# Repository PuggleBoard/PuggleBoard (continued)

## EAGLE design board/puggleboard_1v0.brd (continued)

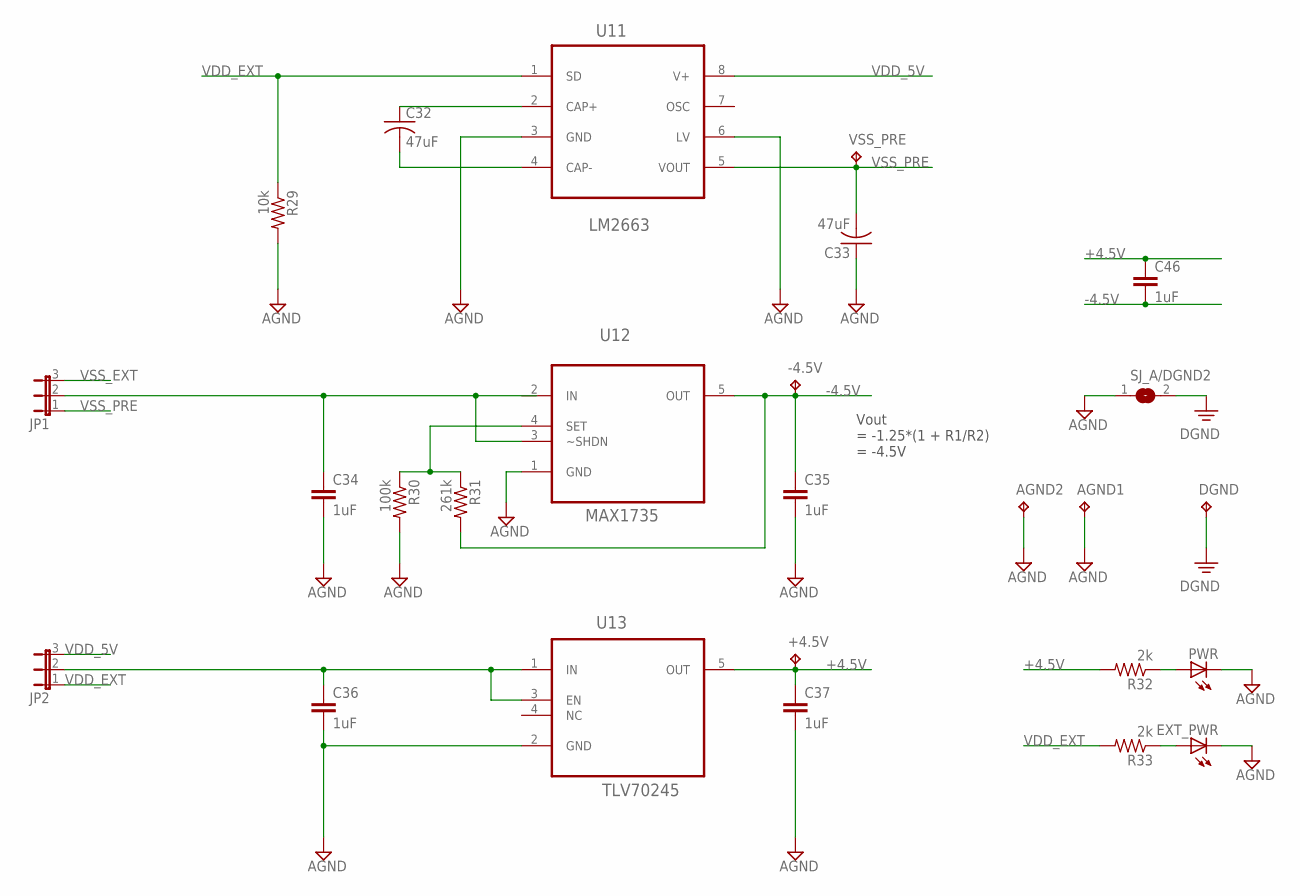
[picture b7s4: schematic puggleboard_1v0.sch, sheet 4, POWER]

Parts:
+4.5V: TPPAD1-17; P1-17
-4.5V: TPB1,27; B1,27
AGND1, AGND2: TPPAD1-17; P1-17
C32, C33: 47uF; C1206
C34, C35, C36, C37, C46: 1uF; C0603
DGND: TPPAD1-17; P1-17
EXT_PWR: LEDCHIPLED_0805; CHIPLED_0805
JP1, JP2: JP2E; JP2
PWR: LEDCHIPLED_0805; CHIPLED_0805
R29: 10k; R0603
R30: 100k; R0603
R31: 261k; R0603
R32, R33: 2k; R0603
SJ_A/DGND2: SJ
U11: LM2663; SOIC127P600X175-8N
U12: MAX1735; SOT95P280X145-5N
U13: TLV70245; SOT95P280X110-5N
VSS_PRE: TPB1,27; B1,27

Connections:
+4.5V: +4.5V.TP, C37.1, C46.1, R32.2, U13.5 (OUT); also elsewhere on the board
-4.5V: -4.5V.TP, C35.1, C46.2, R31.2, U12.5 (OUT); also elsewhere on the board
AGND: AGND1.TP, AGND2.TP, C33.1, C34.2, C35.2, C36.2, C37.2, EXT_PWR.C, PWR.C, R29.2, R30.2, SJ_A/DGND2.1, U11.3 (GND), U11.6 (LV), U12.1 (GND), U13.2 (GND); also elsewhere on the board
DGND: DGND.TP, SJ_A/DGND2.2; also elsewhere on the board
unnamed: R30.1, R31.1, U12.4 (SET)
unnamed: EXT_PWR.A, R33.1
unnamed: C36.1, JP2.2, U13.1 (IN), U13.3 (EN)
unnamed: PWR.A, R32.1
unnamed: C34.1, JP1.2, U12.3 (~SHDN)
unnamed: C32.1, U11.2 (CAP+)
unnamed: C32.2, U11.4 (CAP-)
VDD_5V: JP2.3, U11.8 (V+); also elsewhere on the board
VDD_EXT: JP2.1, R29.1, R33.2, U11.1 (SD); also elsewhere on the board
VSS_EXT: JP1.3; also elsewhere on the board
VSS_PRE: C33.2, JP1.1, U11.5 (VOUT), VSS_PRE.TP

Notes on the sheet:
Vout = -1.25*(1 + R1/R2) = -4.5V

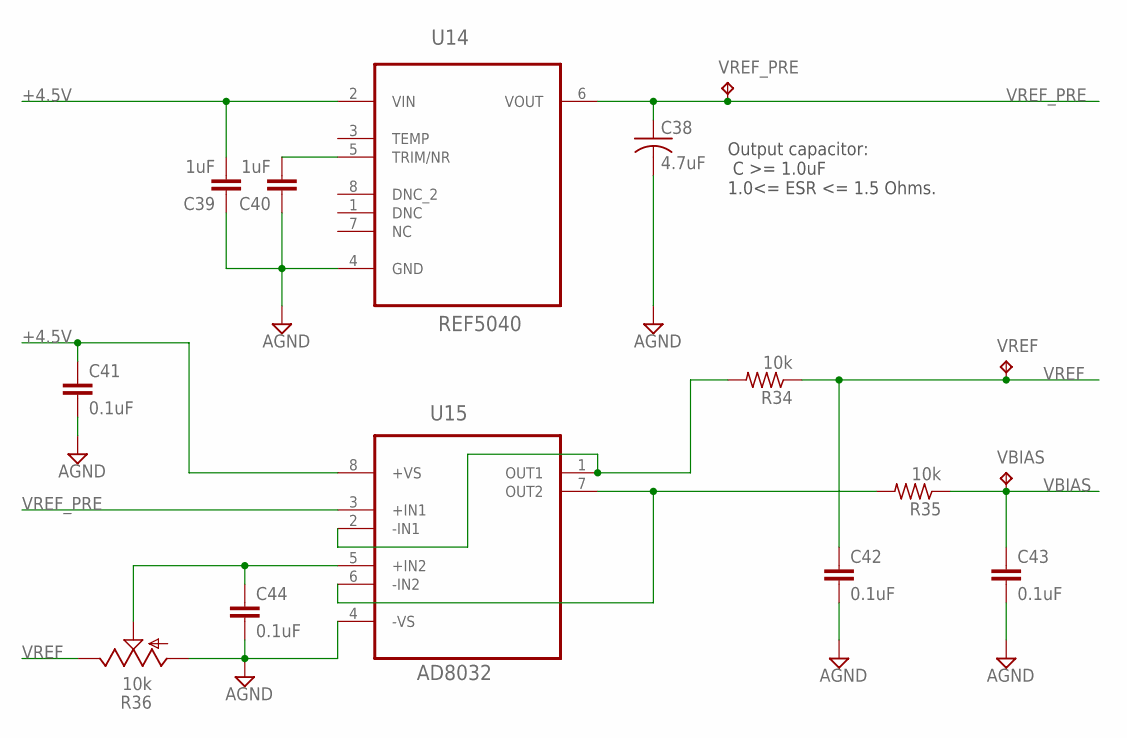
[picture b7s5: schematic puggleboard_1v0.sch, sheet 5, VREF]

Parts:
C38: 4.7uF; C1206
C39, C40: 1uF; C0603
C41, C42, C43, C44: 0.1uF; C0603
R34, R35: 10k; R0603
R36: 10k; M84W-TRIMMER
U14: REF5040; SOIC127P600X175-8N
U15: AD8032; SOIC127P600X175-8N
VBIAS: TPB1,27; B1,27
VREF: TPB1,27; B1,27
VREF_PRE: TPB1,27; B1,27

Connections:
+4.5V: C39.2, C41.1, U14.2 (VIN), U15.8 (+VS); also elsewhere on the board
AGND: C38.2, C39.1, C40.1, C41.2, C42.2, C43.2, C44.2, R36.3 (A), U14.4 (GND), U15.4 (-VS); also elsewhere on the board
unnamed: C44.1, R36.2 (S), U15.5 (+IN2)
unnamed: R35.2, U15.6 (-IN2), U15.7 (OUT2)
unnamed: R34.2, U15.1 (OUT1), U15.2 (-IN1)
unnamed: C40.2, U14.5 (TRIM/NR)
VBIAS: C43.1, R35.1, VBIAS.TP; also elsewhere on the board
VREF: C42.1, R34.1, R36.1 (E), VREF.TP; also elsewhere on the board
VREF_PRE: C38.1, U14.6 (VOUT), U15.3 (+IN1), VREF_PRE.TP

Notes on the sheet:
Output capacitor: C >= 1.0uF 1.0<= ESR <= 1.5 Ohms.

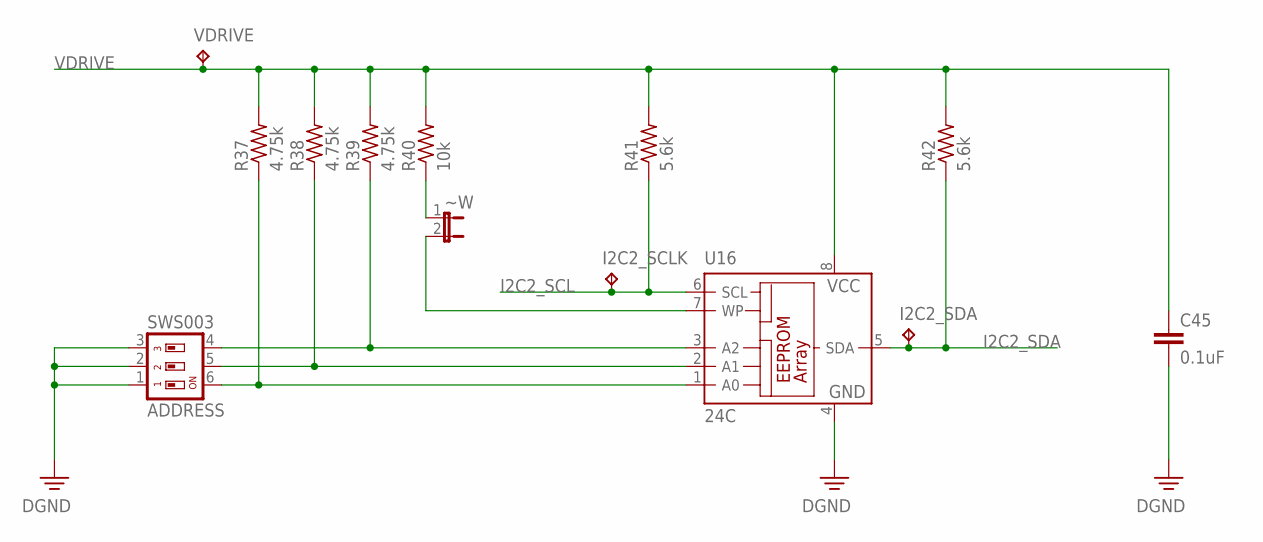
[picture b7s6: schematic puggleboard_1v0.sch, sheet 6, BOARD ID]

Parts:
ADDRESS: SWS003; SMS-003
C45: 0.1uF; C0603
I2C2_SCLK, I2C2_SDA: TPB1,27; B1,27
R37, R38, R39: 4.75k; R0603
R40: 10k; R0603
R41, R42: 5.6k; R0603
U16: 24C; SO-08
VDRIVE: TPPAD1-17; P1-17
~W: JP1E; JP1

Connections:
DGND: ADDRESS.1, ADDRESS.2, ADDRESS.3, C45.2, U16.4 (GND); also elsewhere on the board
I2C2_SCL: I2C2_SCLK.TP, R41.1, U16.6 (SCL); also elsewhere on the board
I2C2_SDA: I2C2_SDA.TP, R42.1, U16.5 (SDA); also elsewhere on the board
unnamed: ADDRESS.6, R37.1, U16.1 (A0)
unnamed: ADDRESS.5, R38.1, U16.2 (A1)
unnamed: ADDRESS.4, R39.1, U16.3 (A2)
unnamed: U16.7 (WP), ~W.2
unnamed: R40.1, ~W.1
VDRIVE: C45.1, R37.2, R38.2, R39.2, R40.2, R41.2, R42.2, U16.8 (VCC), VDRIVE.TP; also elsewhere on the board

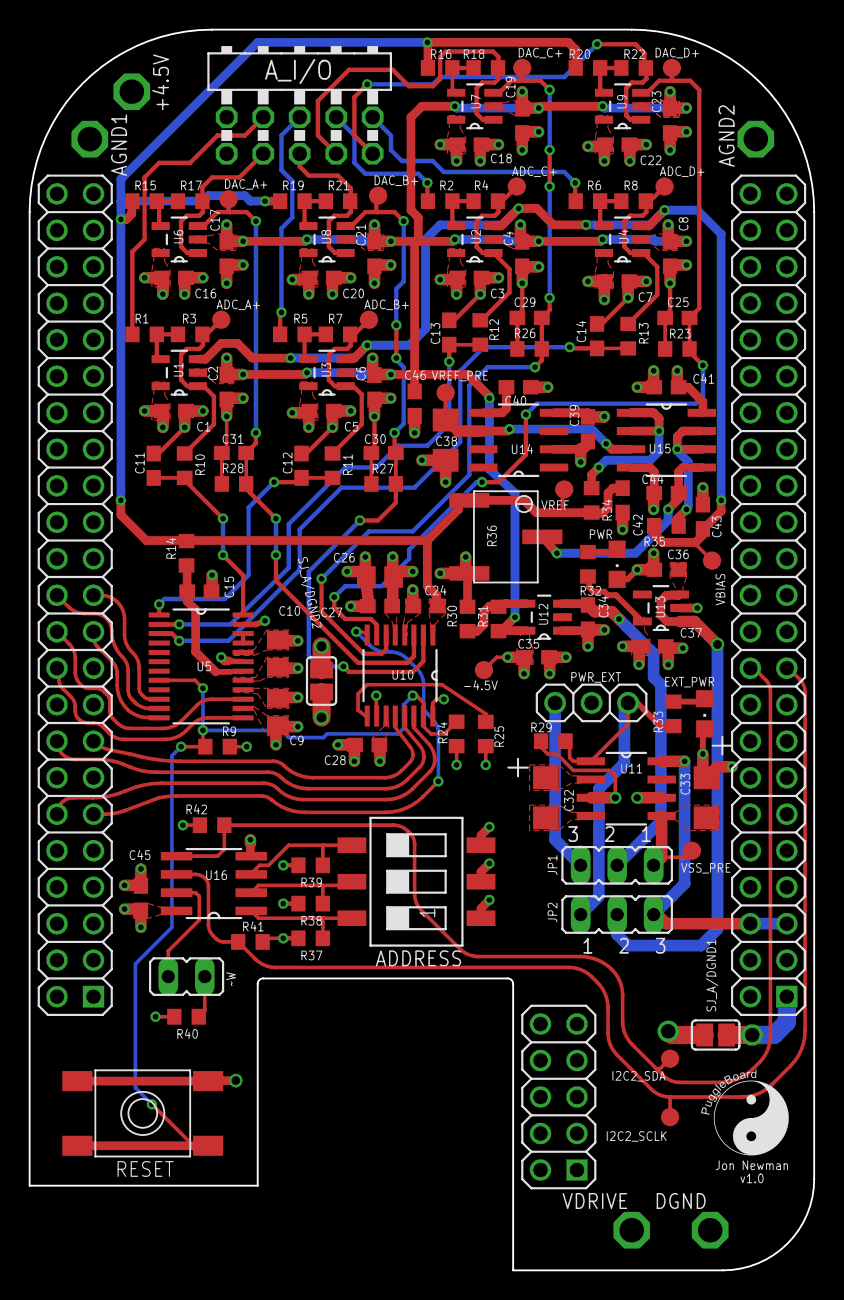
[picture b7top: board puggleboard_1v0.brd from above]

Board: 4 copper layers, 54.6 x 86.4 mm, 136 parts (0 on the bottom side), 73 nets.

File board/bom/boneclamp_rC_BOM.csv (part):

Part,Value,Device,Package,Description,MPN,DKN,,,Manu
ADDRESS,SWS003,SWS003,SMS-003,SMD Dip Switch 3 pol.,219-3LPST,CT2193LPST-ND,,,
A_I/O,PINHD-2X5/90,PINHD-2X5/90,2X05/90,2X5 0.1 inch male header,68021-210HLF,609-3410-ND,,,
C1,0.1uF,C-EUC0603,C0603,"CAPACITOR, European symbol",C1608X7R1E104K080AA,445-1316-1-ND,,,
C2,0.1uF,C-EUC0603,C0603,"CAPACITOR, European symbol",C1608X7R1E104K080AA,445-1316-1-ND,,,
C3,0.1uF,C-EUC0603,C0603,"CAPACITOR, European symbol",C1608X7R1E104K080AA,445-1316-1-ND,,,
C4,0.1uF,C-EUC0603,C0603,"CAPACITOR, European symbol",C1608X7R1E104K080AA,445-1316-1-ND,,,
C5,0.1uF,C-EUC0603,C0603,"CAPACITOR, European symbol",C1608X7R1E104K080AA,445-1316-1-ND,,,
C6,0.1uF,C-EUC0603,C0603,"CAPACITOR, European symbol",C1608X7R1E104K080AA,445-1316-1-ND,,,
C7,0.1uF,C-EUC0603,C0603,"CAPACITOR, European symbol",C1608X7R1E104K080AA,445-1316-1-ND,,,
C8,0.1uF,C-EUC0603,C0603,"CAPACITOR, European symbol",C1608X7R1E104K080AA,445-1316-1-ND,,,
C9,4.7uF,C-EUC0805,C0805,"CAPACITOR, European symbol",TMK212AB7475KG-T,587-2990-1-ND,,,
C10,4.7uF,C-EUC0805,C0805,"CAPACITOR, European symbol",TMK212AB7475KG-T,587-2990-1-ND,,,
C11,1nF,C-EUC0603,C0603,"CAPACITOR, European symbol",C0603C102K3RACTU,399-7834-1-ND,,,
C12,1nF,C-EUC0603,C0603,"CAPACITOR, European symbol",C0603C102K3RACTU,399-7834-1-ND,,,
C13,1nF,C-EUC0603,C0603,"CAPACITOR, European symbol",C0603C102K3RACTU,399-7834-1-ND,,,
C14,1nF,C-EUC0603,C0603,"CAPACITOR, European symbol",C0603C102K3RACTU,399-7834-1-ND,,,
C15,22uF,C-EUC0603,C0603,"CAPACITOR, European symbol",C2012X5R1A226M125AB,445-7665-1-ND,,,
C16,0.1uF,C-EUC0603,C0603,"CAPACITOR, European symbol",C1608X7R1E104K080AA,445-1316-1-ND,,,
C17,0.1uF,C-EUC0603,C0603,"CAPACITOR, European symbol",C1608X7R1E104K080AA,445-1316-1-ND,,,
C18,0.1uF,C-EUC0603,C0603,"CAPACITOR, European symbol",C1608X7R1E104K080AA,445-1316-1-ND,,,
C19,0.1uF,C-EUC0603,C0603,"CAPACITOR, European symbol",C1608X7R1E104K080AA,445-1316-1-ND,,,
C20,0.1uF,C-EUC0603,C0603,"CAPACITOR, European symbol",C1608X7R1E104K080AA,445-1316-1-ND,,,
C21,0.1uF,C-EUC0603,C0603,"CAPACITOR, European symbol",C1608X7R1E104K080AA,445-1316-1-ND,,,
C22,0.1uF,C-EUC0603,C0603,"CAPACITOR, European symbol",C1608X7R1E104K080AA,445-1316-1-ND,,,
C23,0.1uF,C-EUC0603,C0603,"CAPACITOR, European symbol",C1608X7R1E104K080AA,445-1316-1-ND,,,
C24,0.1uF,C-EUC0603,C0603,"CAPACITOR, European symbol",C1608X7R1E104K080AA,445-1316-1-ND,,,
C25,,C-EUC0603,C0603,"CAPACITOR, European symbol",,,,,
C26,10uF,C-USC0805,C0805,"CAPACITOR, American symbol",TAJP106M010RNJ,478-3281-1-ND,,,
C27,0.1uF,C-EUC0603,C0603,"CAPACITOR, European symbol",C1608X7R1E104K080AA,445-1316-1-ND,,,
C28,0.1uF,C-EUC0603,C0603,"CAPACITOR, European symbol",C1608X7R1E104K080AA,445-1316-1-ND,,,
C29,,C-EUC0603,C0603,"CAPACITOR, European symbol",,,,,
C30,,C-EUC0603,C0603,"CAPACITOR, European symbol",,,,,
C31,,C-EUC0603,C0603,"CAPACITOR, European symbol",,,,,
C32,47uF,C-USC1206,C1206,"CAPACITOR, American symbol",T520A476M004ATE070,399-4714-1-ND,,,
C33,47uF,C-USC1206,C1206,"CAPACITOR, American symbol",T520A476M004ATE070,399-4714-1-ND,,,
C34,1uF,C-EUC0603,C0603,"CAPACITOR, European symbol",C0805C105K4RACTU,399-1284-1-ND,,,
C35,1uF,C-EUC0603,C0603,"CAPACITOR, European symbol",C0805C105K4RACTU,399-1284-1-ND,,,
C36,1uF,C-EUC0603,C0603,"CAPACITOR, European symbol",C0805C105K4RACTU,399-1284-1-ND,,,
C37,1uF,C-EUC0603,C0603,"CAPACITOR, European symbol",C0805C105K4RACTU,399-1284-1-ND,,,
C38,4.7uF,C-EUC0603,C1206,"CAPACITOR, European symbol",TR3A475K010C1400,718-1757-1-ND,,,
C39,1uF,C-EUC0603,C0603,"CAPACITOR, European symbol",C0805C105K4RACTU,399-1284-1-ND,,,
C40,1uF,C-EUC0603,C0603,"CAPACITOR, European symbol",C0805C105K4RACTU,399-1284-1-ND,,,
C41,0.1uF,C-EUC0603,C0603,"CAPACITOR, European symbol",C1608X7R1E104K080AA,445-1316-1-ND,,,
C42,0.1uF,C-EUC0603,C0603,"CAPACITOR, European symbol",C1608X7R1E104K080AA,445-1316-1-ND,,,
C43,0.1uF,C-EUC0603,C0603,"CAPACITOR, European symbol",C1608X7R1E104K080AA,445-1316-1-ND,,,
C44,0.1uF,C-EUC0603,"C0,603","CAPACITOR, European symbol",C1608X7R1E104K080AA,445-1316-1-ND,,,
C45,0.1uF,C-EUC0603,C0603,"CAPACITOR, European symbol",C1608X7R1E104K080AA,445-1316-1-ND,,,
EXT_PWR,,LEDCHIPLED_0805,CHIPLED_0805,LED,598-8140-107F,350-2041-1-ND,,,
JP1,,JP2E,JP2,JUMPER,87224-3,A26545-ND,,,
JP2,,JP2E,JP2,JUMPER,87224-3,A26545-ND,,,
JP3,,JP1E,JP1,JUMPER,87224-3,A26545-ND,,,
PWR,,LEDCHIPLED_0805,CHIPLED_0805,LED,598-8170-107F,350-2044-1-ND,,,
PWR_EXT,,PINHD-1X3,1X03,PIN HEADER,3M9468-ND,961103-5604-AR,,,
R1,20k,R-US_R0603,R0603,"RESISTOR, American symbol",MCT06030C2002FP500,MCT0603-20.0K-CFCT-ND,,,
R2,20k,R-US_R0603,R0603,"RESISTOR, American symbol",MCT06030C2002FP500,MCT0603-20.0K-CFCT-ND,,,
R3,10k,R-US_R0603,R0603,"RESISTOR, American symbol",MCT06030C1002FP500,MCT0603-10.0K-CFCT-ND,,,
R4,10k,R-US_R0603,R0603,"RESISTOR, American symbol",MCT06030C1002FP500,MCT0603-10.0K-CFCT-ND,,,
R5,20k,R-US_R0603,R0603,"RESISTOR, American symbol",MCT06030C2002FP500,MCT0603-20.0K-CFCT-ND,,,
R6,20k,R-US_R0603,R0603,"RESISTOR, American symbol",MCT06030C2002FP500,MCT0603-20.0K-CFCT-ND,,,
R7,10k,R-US_R0603,R0603,"RESISTOR, American symbol",MCT06030C1002FP500,MCT0603-10.0K-CFCT-ND,,,
R8,10k,R-US_R0603,R0603,"RESISTOR, American symbol",MCT06030C1002FP500,MCT0603-10.0K-CFCT-ND,,,
R9,10k,R-US_R0603,R0603,"RESISTOR, American symbol",CRCW060310K0JNEA,541-10KGCT-ND,,,
R10,20,R-US_R0603,R0603,"RESISTOR, American symbol",RMCF0603FT20R0,RMCF0603FT20R0CT-ND,,,
R11,20,R-US_R0603,R0603,"RESISTOR, American symbol",RMCF0603FT20R0,RMCF0603FT20R0CT-ND,,,
R12,20,R-US_R0603,R0603,"RESISTOR, American symbol",RMCF0603FT20R0,RMCF0603FT20R0CT-ND,,,
R13,20,R-US_R0603,R0603,"RESISTOR, American symbol",RMCF0603JT20R0,RMCF0603JT20R0CT-ND,,,
R14,10,R-US_R0603,R0603,"RESISTOR, American symbol",RMCF0603JT10R0,RMCF0603JT10R0CT-ND,,,
R15,10k,R-US_R0603,R0603,"RESISTOR, American symbol",MCT06030C1002FP500,MCT0603-10.0K-CFCT-ND,,,
R16,10k,R-US_R0603,R0603,"RESISTOR, American symbol",MCT06030C1002FP500,MCT0603-10.0K-CFCT-ND,,,
R17,10k,R-US_R0603,R0603,"RESISTOR, American symbol",MCT06030C1002FP500,MCT0603-10.0K-CFCT-ND,,,
R18,10k,R-US_R0603,R0603,"RESISTOR, American symbol",MCT06030C1002FP500,MCT0603-10.0K-CFCT-ND,,,
R19,10k,R-US_R0603,R0603,"RESISTOR, American symbol",MCT06030C1002FP500,MCT0603-10.0K-CFCT-ND,,,
R20,10k,R-US_R0603,R0603,"RESISTOR, American symbol",MCT06030C1002FP500,MCT0603-10.0K-CFCT-ND,,,
R21,10k,R-US_R0603,R0603,"RESISTOR, American symbol",MCT06030C1002FP500,MCT0603-10.0K-CFCT-ND,,,
R22,10k,R-US_R0603,R0603,"RESISTOR, American symbol",MCT06030C1002FP500,MCT0603-10.0K-CFCT-ND,,,
R23,,R-US_R0603,R0603,"RESISTOR, American symbol",,,,,
R24,10k,R-US_R0603,R0603,"RESISTOR, American symbol",CRCW060310K0JNEA,541-10KGCT-ND,,,
R25,10k,R-US_R0603,R0603,"RESISTOR, American symbol",CRCW060310K0JNEA,541-10KGCT-ND,,,
R26,,R-US_R0603,R0603,"RESISTOR, American symbol",,,,,
R27,,R-US_R0603,R0603,"RESISTOR, American symbol",,,,,
R28,,R-US_R0603,R0603,"RESISTOR, American symbol",,,,,
R29,10k,R-US_R0603,R0603,"RESISTOR, American symbol",CRCW060310K0JNEA,541-10KGCT-ND,,,
R30,100k,R-US_R0603,R0603,"RESISTOR, American symbol",RMCF0603JT100K,RMCF0603JT100KCT-ND,,,
R31,260k,R-US_R0603,R0603,"RESISTOR, American symbol",P261KHCT-ND,ERJ-3EKF2613V,,,
R32,2k,R-US_R0603,R0603,"RESISTOR, American symbol",RMCF0603JT2K00,RMCF0603JT2K00CT-ND,,,
R33,2k,R-US_R0603,R0603,"RESISTOR, American symbol",RMCF0603JT2K00,RMCF0603JT2K00CT-ND,,,
R34,10k,R-US_R0603,R0603,"RESISTOR, American symbol",CRCW060310K0JNEA,541-10KGCT-ND,,,
R35,10k,R-US_R0603,R0603,"RESISTOR, American symbol",CRCW060310K0JNEA,541-10KGCT-ND,,,
R36,10k,TRIM_US-,M84-TRIMMER,POTENTIOMETER,84PR10KLF,987-1152-ND,,,
R37,4.75k,R-US_R0603,R0603,"RESISTOR, American symbol",RMCF0603FT4K75,RMCF0603FT4K75CT-ND,,,
R38,4.75k,R-US_R0603,R0603,"RESISTOR, American symbol",RMCF0603FT4K75,RMCF0603FT4K75CT-ND,,,
R39,4.75k,R-US_R0603,R0603,"RESISTOR, American symbol",RMCF0603FT4K75,RMCF0603FT4K75CT-ND,,,
R40,10k,R-US_R0603,R0603,"RESISTOR, American symbol",CRCW060310K0JNEA,541-10KGCT-ND,,,
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
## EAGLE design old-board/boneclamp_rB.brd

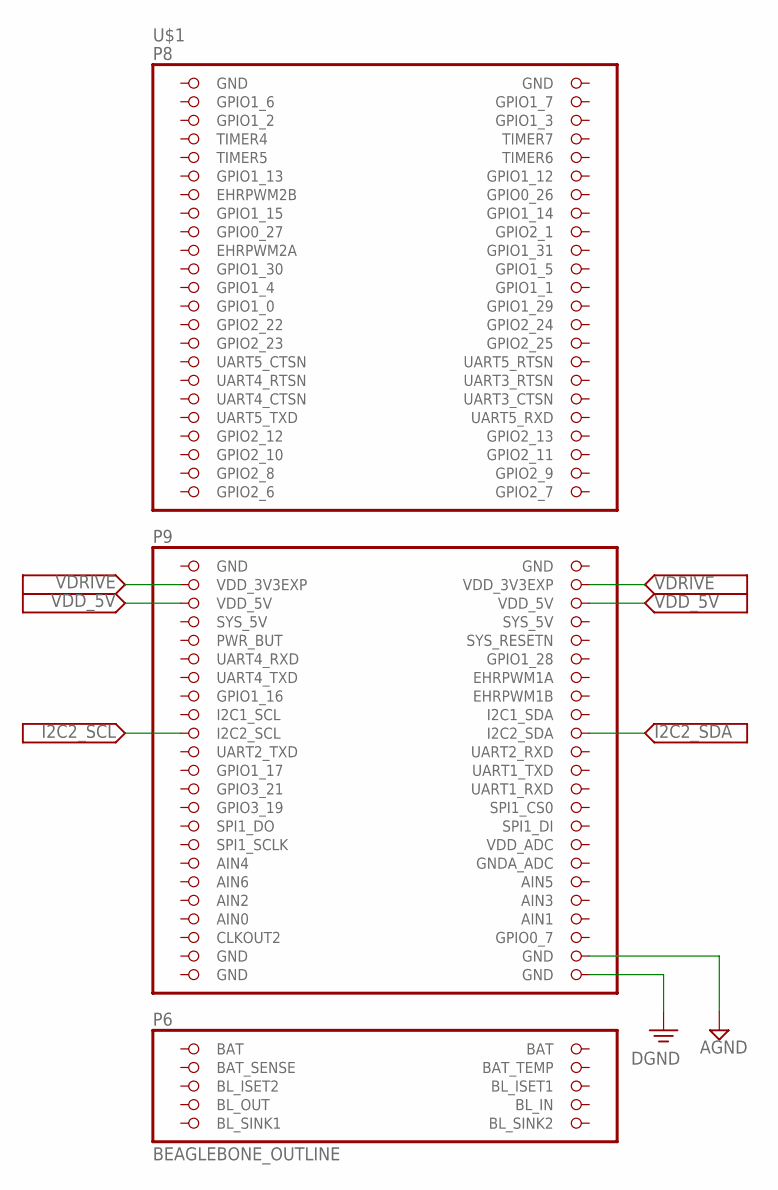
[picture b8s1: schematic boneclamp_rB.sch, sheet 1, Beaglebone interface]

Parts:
U$1: BEAGLEBONE_OUTLINE; BEAGLEBONE_SHIELD

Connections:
AGND: U$1.90 (GND); also elsewhere on the board
AIN0: U$1.85 (AIN0)
BAT_SENSE: U$1.95 (BAT_SENSE)
BL_IN: U$1.97 (BL_IN)
BL_OUT: U$1.100 (BL_OUT)
BL_SINK1: U$1.101 (BL_SINK1)
BL_SINK2: U$1.102 (BL_SINK2)
DGND: U$1.92 (GND); also elsewhere on the board
GND: U$1.1 (GND), U$1.2 (GND), U$1.47 (GND), U$1.48 (GND), U$1.89 (GND), U$1.91 (GND); also elsewhere on the board
I2C2_SCL: U$1.65 (I2C2_SCL); also elsewhere on the board
I2C2_SDA: U$1.66 (I2C2_SDA); also elsewhere on the board
SYS_5V: U$1.53 (SYS_5V)
VDD_5V: U$1.51 (VDD_5V), U$1.52 (VDD_5V); also elsewhere on the board
VDRIVE: U$1.49 (VDD_3V3EXP), U$1.50 (VDD_3V3EXP); also elsewhere on the board

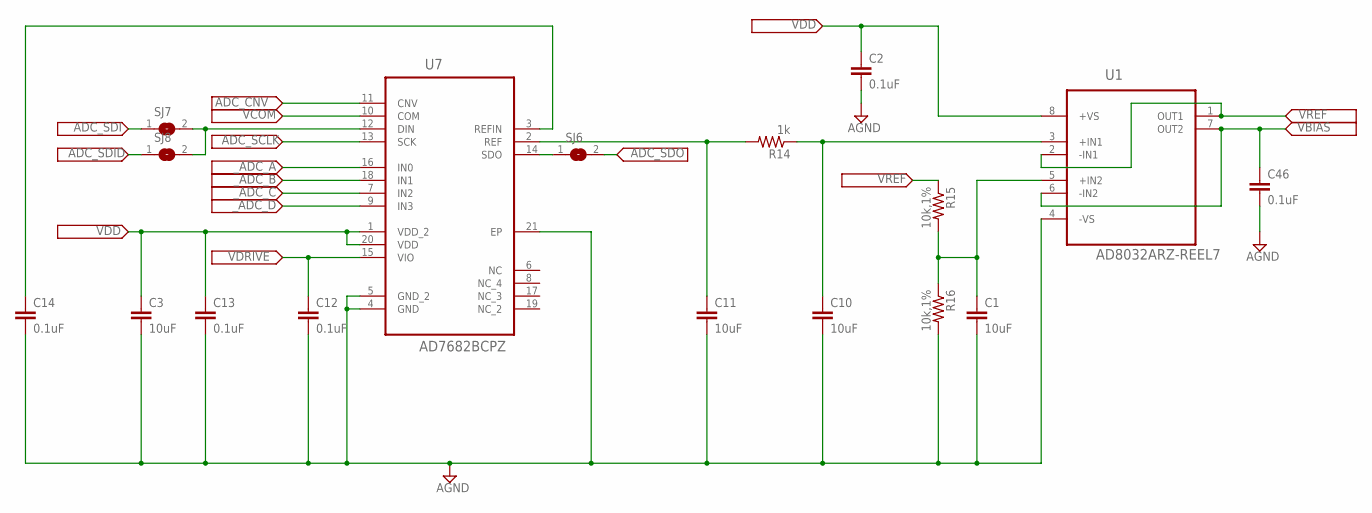
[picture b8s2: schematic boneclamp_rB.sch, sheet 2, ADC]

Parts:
C1, C3, C10, C11: 10uF; C0805
C2, C12, C13, C14, C46: 0.1uF; C0805
R14: 1k; R0805
R15, R16: 10k,1%; R0805
SJ6, SJ7, SJ8: SJ
U1: AD8032ARZ-REEL7; SOIC127P600X175-8N
U7: AD7682BCPZ; QFN50P400X400X100-21N

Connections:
ADC_CNV: U7.11 (CNV)
ADC_SCLK: U7.13 (SCK)
ADC_SDI: SJ7.1
ADC_SDID: SJ8.1
ADC_SDO: SJ6.2
AGND: C1.2, C2.2, C3.2, C10.2, C11.2, C12.2, C13.2, C14.2, C46.2, R16.2, U1.4 (-VS), U7.4 (GND), U7.5 (GND_2), U7.21 (EP); also elsewhere on the board
unnamed: C1.1, R15.2, R16.1, U1.5 (+IN2)
unnamed: SJ7.2, SJ8.2, U7.12 (DIN)
unnamed: C11.1, R14.2, U7.2 (REF)
unnamed: C10.1, R14.1, U1.3 (+IN1)
unnamed: C14.1, U7.3 (REFIN)
VBIAS: C46.1, U1.6 (-IN2), U1.7 (OUT2); also elsewhere on the board
VCOM: U7.10 (COM)
VDD: C2.1, C3.1, C13.1, U1.8 (+VS), U7.1 (VDD_2), U7.20 (VDD); also elsewhere on the board
VDRIVE: C12.1, U7.15 (VIO); also elsewhere on the board
VREF: R15.1, U1.1 (OUT1), U1.2 (-IN1); also elsewhere on the board
_ADC_A: U7.16 (IN0); also elsewhere on the board
_ADC_B: U7.18 (IN1); also elsewhere on the board
_ADC_C: U7.7 (IN2); also elsewhere on the board
_ADC_D: U7.9 (IN3); also elsewhere on the board

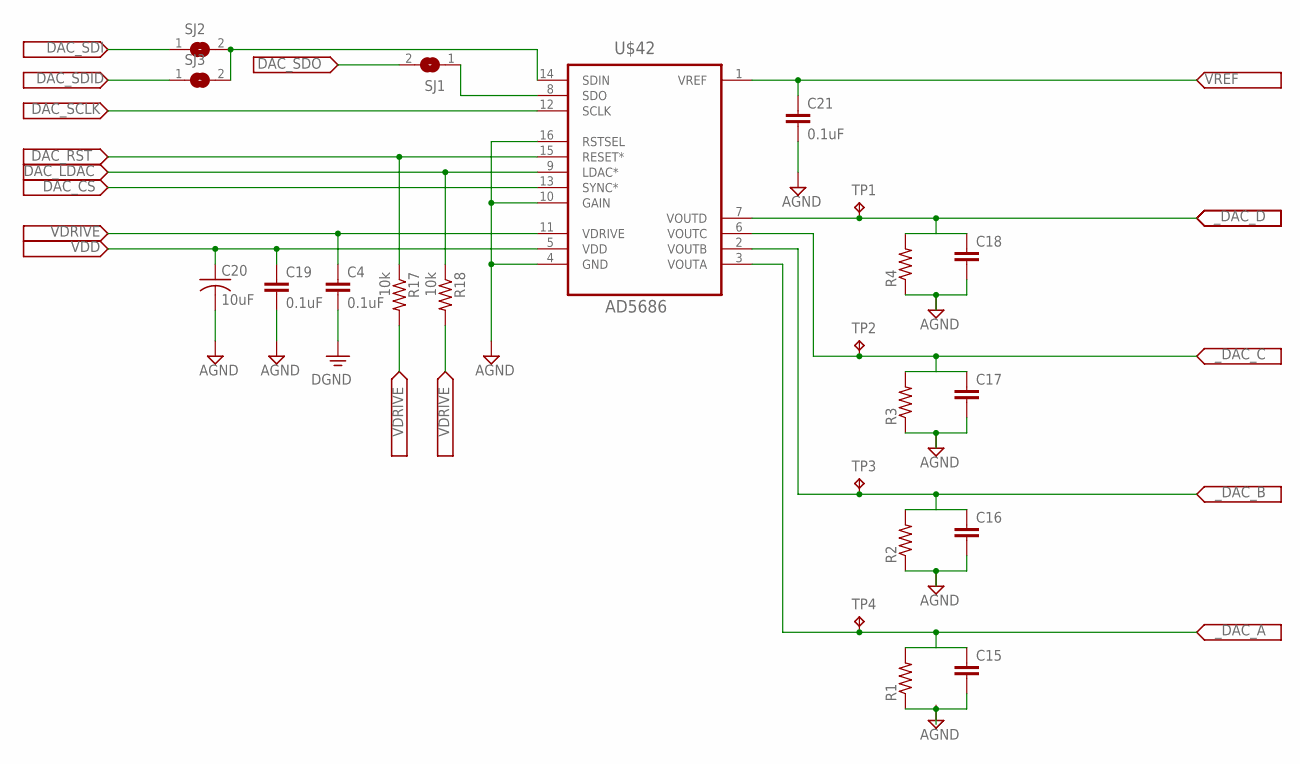
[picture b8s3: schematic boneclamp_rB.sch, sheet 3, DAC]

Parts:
C4, C19, C21: 0.1uF; C0805
C15, C16, C17, C18: C-EUC0805; C0805
C20: 10uF; C0805
R1, R2, R3, R4: R-US_R0805; R0805
R17, R18: 10k; R0805
SJ1, SJ2, SJ3: SJ
TP1, TP2, TP3, TP4: TPB1,27; B1,27
U$42: AD5686; MO-153-AB

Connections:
AGND: C16.2, C17.2, C18.2, C19.2, C20.2, C21.2, R2.1, R3.1, R4.1, U$42.4 (GND), U$42.10 (GAIN), U$42.16 (RSTSEL); also elsewhere on the board
DAC_CS: U$42.13 (SYNC*)
DAC_LDAC: R18.1, U$42.9 (LDAC*)
DAC_RST: R17.1, U$42.15 (RESET*)
DAC_SCLK: U$42.12 (SCLK)
DAC_SDI: SJ2.1
DAC_SDID: SJ3.1
DAC_SDO: SJ1.2
unnamed: SJ1.1, U$42.8 (SDO)
unnamed: SJ2.2, SJ3.2, U$42.14 (SDIN)
unnamed: C15.2, R1.1
PE: C4.2
VDD: C19.1, C20.1, U$42.5 (VDD); also elsewhere on the board
VDRIVE: C4.1, R17.2, R18.2, U$42.11 (VDRIVE); also elsewhere on the board
VREF: C21.1, U$42.1 (VREF); also elsewhere on the board
_DAC_A: C15.1, R1.2, TP4.TP, U$42.3 (VOUTA); also elsewhere on the board
_DAC_B: C16.1, R2.2, TP3.TP, U$42.2 (VOUTB); also elsewhere on the board
_DAC_C: C17.1, R3.2, TP2.TP, U$42.6 (VOUTC); also elsewhere on the board
_DAC_D: C18.1, R4.2, TP1.TP, U$42.7 (VOUTD); also elsewhere on the board

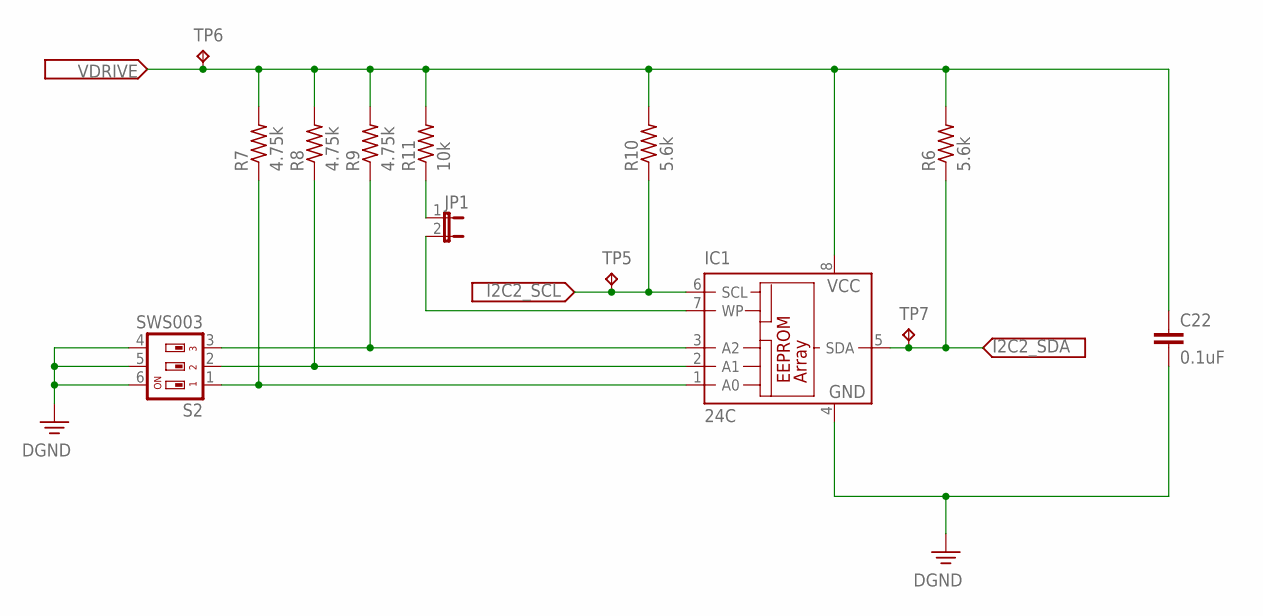
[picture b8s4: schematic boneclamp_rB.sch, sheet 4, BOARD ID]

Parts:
C22: 0.1uF; C0603
IC1: 24C; SO-08
JP1: JP1E; JP1
R6, R10: 5.6k; R0603
R7, R8, R9: 4.75k; R0603
R11: 10k; R0603
S2: SWS003; SMS-003
TP5, TP6, TP7: TPB1,27; B1,27

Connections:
DGND: C22.2, IC1.4 (GND), S2.4, S2.5, S2.6; also elsewhere on the board
I2C2_SCL: IC1.6 (SCL), R10.1, TP5.TP; also elsewhere on the board
I2C2_SDA: IC1.5 (SDA), R6.1, TP7.TP; also elsewhere on the board
unnamed: IC1.1 (A0), R7.1, S2.1
unnamed: IC1.2 (A1), R8.1, S2.2
unnamed: IC1.3 (A2), R9.1, S2.3
unnamed: IC1.7 (WP), JP1.2
unnamed: JP1.1, R11.1
VDRIVE: C22.1, IC1.8 (VCC), R6.2, R7.2, R8.2, R9.2, R10.2, R11.2, TP6.TP; also elsewhere on the board

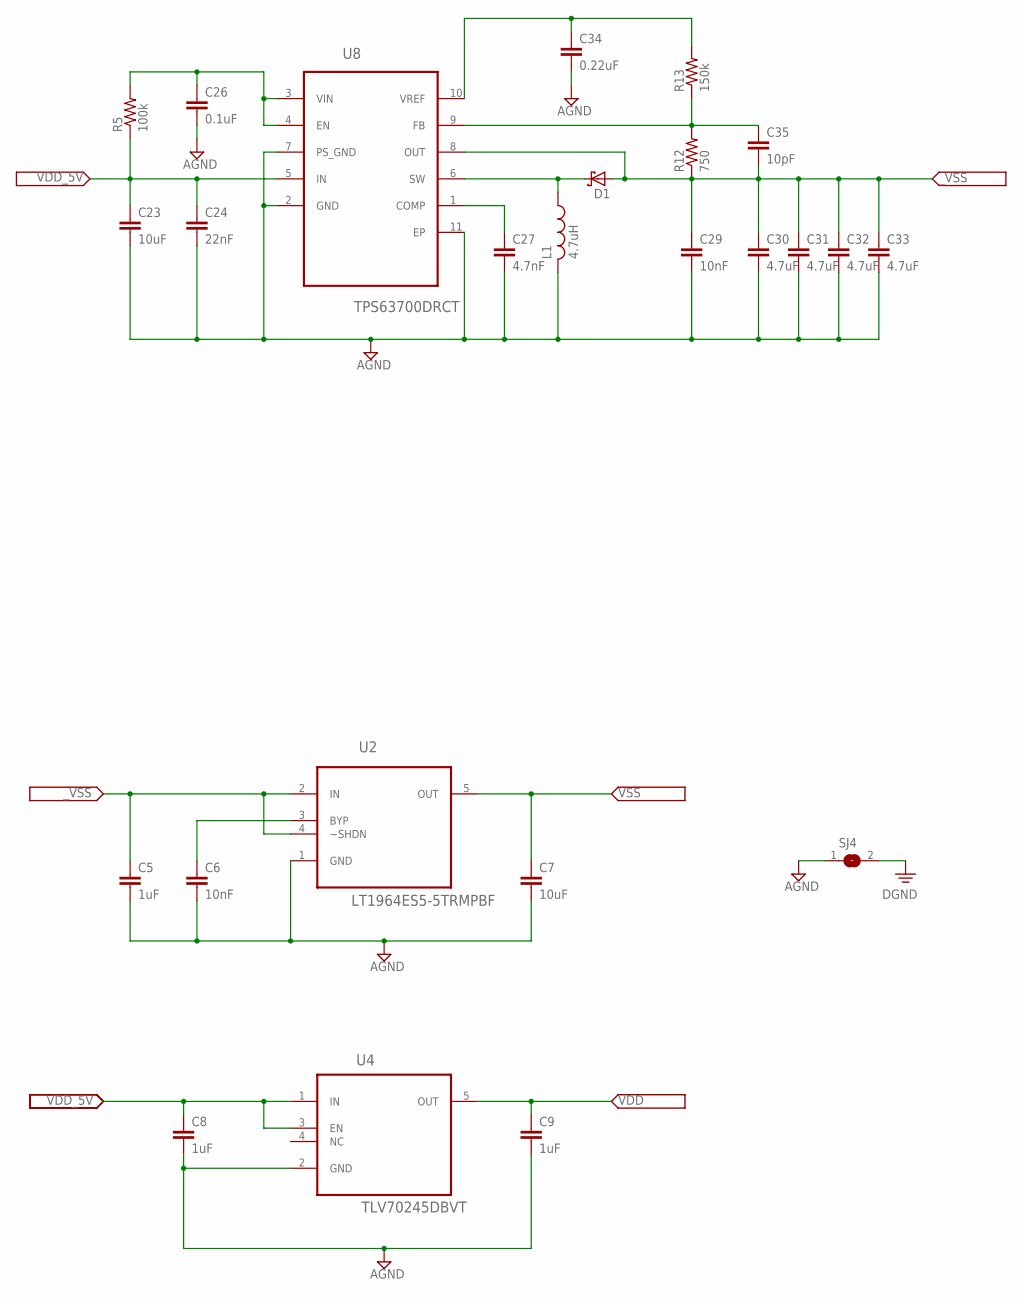
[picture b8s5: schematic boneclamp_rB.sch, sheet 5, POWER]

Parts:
C5, C8, C9: 1uF; C0603
C6, C29: 10nF; C0603
C7, C23: 10uF; C0603
C24: 22nF; C0603
C26: 0.1uF; C0603
C27: 4.7nF; C0603
C30, C31, C32, C33: 4.7uF; C0603
C34: 0.22uF; C0603
C35: 10pF; C0603
D1: SCHOTTKY-DIODE-2; DO-219AB
L1: 4.7uH; L4012M
R5: 100k; R0603
R12: 750; R0603
R13: 150k; R0603
SJ4: SJ
U2: LT1964ES5-5TRMPBF; SOT95P280X100-5N
U4: TLV70245DBVT; SOT95P280X110-5N
U8: TPS63700DRCT; SON50P300X300X100-11N

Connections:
AGND: C5.2, C6.2, C7.2, C8.2, C9.2, C23.2, C24.2, C26.2, C27.2, C29.2, C30.2, C31.2, C32.2, C33.2, C34.2, L1.2, SJ4.1, U2.1 (GND), U4.2 (GND), U8.2 (GND), U8.7 (PS_GND), U8.11 (EP); also elsewhere on the board
DGND: SJ4.2; also elsewhere on the board
unnamed: C6.1, U2.3 (BYP)
unnamed: C26.1, R5.2, U8.3 (VIN), U8.4 (EN)
unnamed: C27.1, U8.1 (COMP)
unnamed: D1.P$1 (A), L1.1, U8.6 (SW)
unnamed: C35.1, R12.2, R13.1, U8.9 (FB)
unnamed: C34.1, R13.2, U8.10 (VREF)
VDD: C9.1, U4.5 (OUT); also elsewhere on the board
VDD_5V: C8.1, C23.1, C24.1, R5.1, U4.1 (IN), U4.3 (EN), U8.5 (IN); also elsewhere on the board
VSS: C7.1, U2.5 (OUT); also elsewhere on the board
_VSS: C5.1, C29.1, C30.1, C31.1, C32.1, C33.1, C35.2, D1.P$2 (C), R12.1, U2.2 (IN), U2.4 (~SHDN), U8.8 (OUT)
